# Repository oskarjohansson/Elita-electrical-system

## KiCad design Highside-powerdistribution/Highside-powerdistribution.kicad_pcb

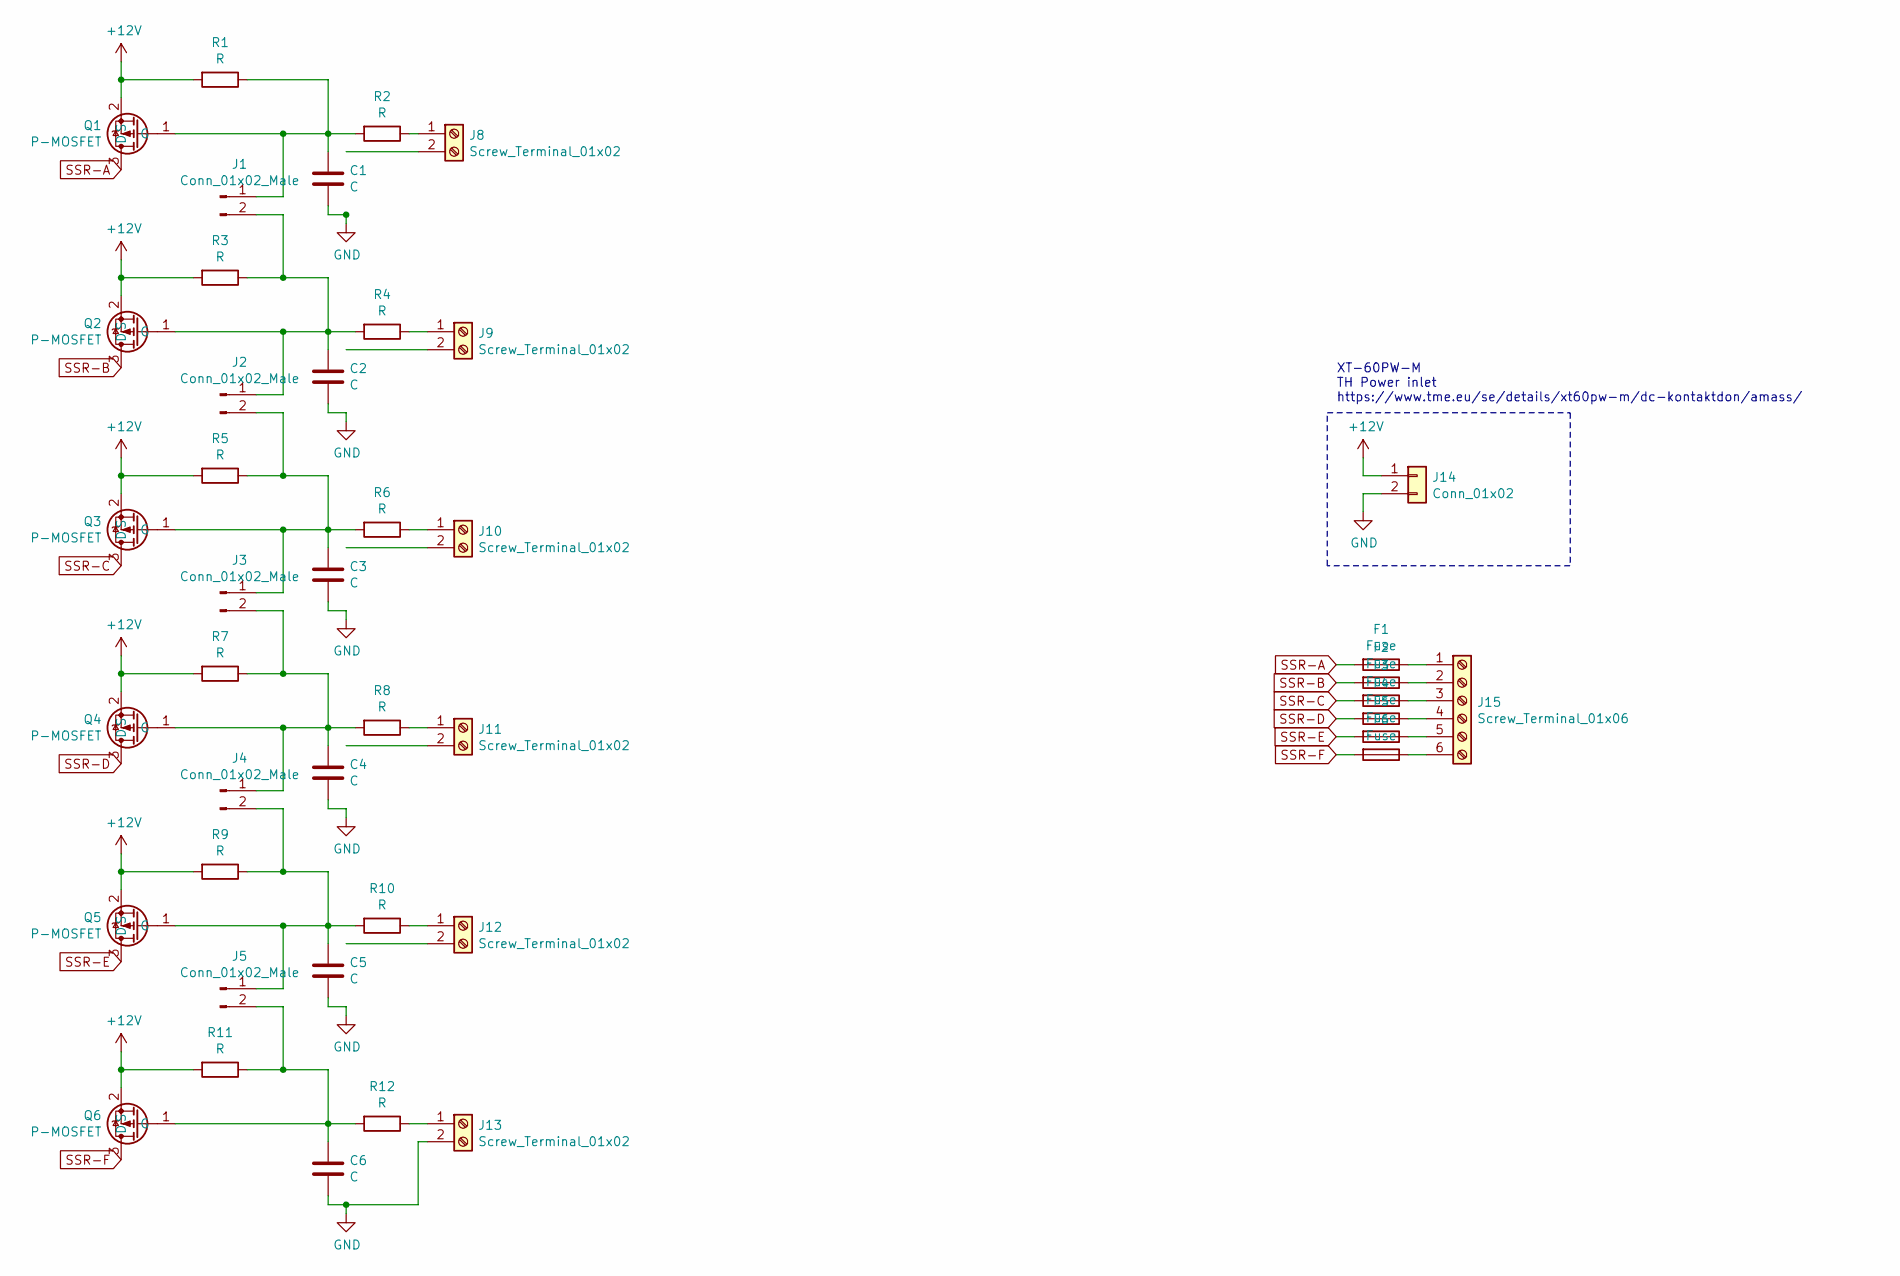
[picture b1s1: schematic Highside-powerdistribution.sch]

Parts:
C1, C2, C3, C4, C5, C6: C; C_0603_1608Metric_Pad1.05x0.95mm_HandSolder
F1, F2, F3, F4, F5, F6: Fuse; ATO_Fuseholder_3522-2
J1, J2, J3, J4, J5: Conn_01x02_Male; PinHeader_1x02_P2.54mm_Vertical
J8, J9, J10, J11, J12, J13: Screw_Terminal_01x02; PTSA1,5-2-3,5-Z
J14: Conn_01x02; Phoenix_TB_2-1935776
J15: Screw_Terminal_01x06; 20.101M-6
Q1, Q2, Q3, Q4, Q5, Q6: P-MOSFET; PG-TO263-3-2
R1, R2, R3, R4, R5, R6, R7, R8, R9, R10, R11, R12: R; R_0603_1608Metric_Pad1.05x0.95mm_HandSolder

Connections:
+12V: J14.1, Q1.2 (S), Q2.2 (S), Q3.2 (S), Q4.2 (S), Q5.2 (S), Q6.2 (S), R1.2, R3.2, R5.2, R7.2, R9.2, R11.2
GND: C1.2, C2.2, C3.2, C4.2, C5.2, C6.2, J8.2, J9.2, J10.2, J11.2, J12.2, J13.2, J14.2
unnamed: C1.1, J1.1, Q1.1 (G), R1.1, R2.2
unnamed: C2.1, J1.2, J2.1, Q2.1 (G), R3.1, R4.2
unnamed: C3.1, J2.2, J3.1, Q3.1 (G), R5.1, R6.2
unnamed: C4.1, J3.2, J4.1, Q4.1 (G), R7.1, R8.2
unnamed: C5.1, J4.2, J5.1, Q5.1 (G), R9.1, R10.2
unnamed: C6.1, J5.2, Q6.1 (G), R11.1, R12.2
unnamed: F1.1, J15.1
unnamed: F2.1, J15.2
unnamed: F3.1, J15.3
unnamed: F4.1, J15.4
unnamed: F5.1, J15.5
unnamed: F6.1, J15.6
unnamed: J8.1, R2.1
unnamed: J9.1, R4.1
unnamed: J10.1, R6.1
unnamed: J11.1, R8.1
unnamed: J12.1, R10.1
unnamed: J13.1, R12.1
SSR-A: F1.2, Q1.3 (D)
SSR-B: F2.2, Q2.3 (D)
SSR-C: F3.2, Q3.3 (D)
SSR-D: F4.2, Q4.3 (D)
SSR-E: F5.2, Q5.3 (D)
SSR-F: F6.2, Q6.3 (D)

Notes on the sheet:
XT-60PW-M TH Power inlet https://www.tme.eu/se/details/xt60pw-m/dc-kontaktdon/amass/

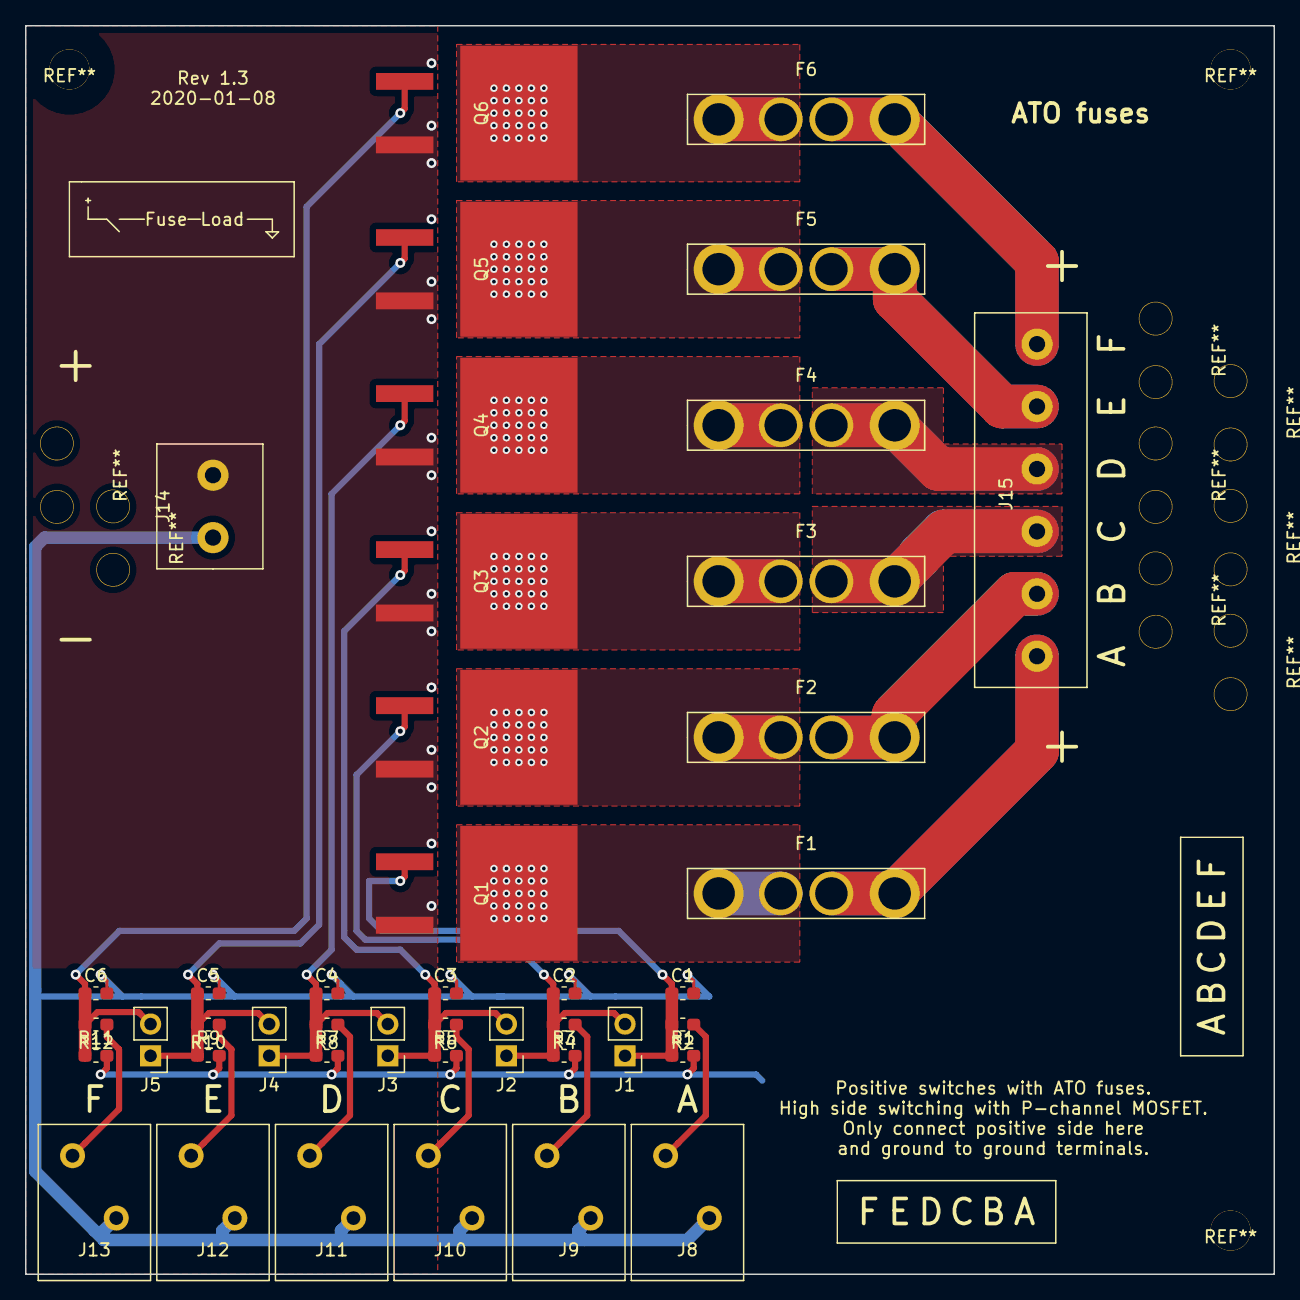
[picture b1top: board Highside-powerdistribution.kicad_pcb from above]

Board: 2 copper layers, 100.0 x 100.0 mm, 43 parts (0 on the bottom side), 26 nets.

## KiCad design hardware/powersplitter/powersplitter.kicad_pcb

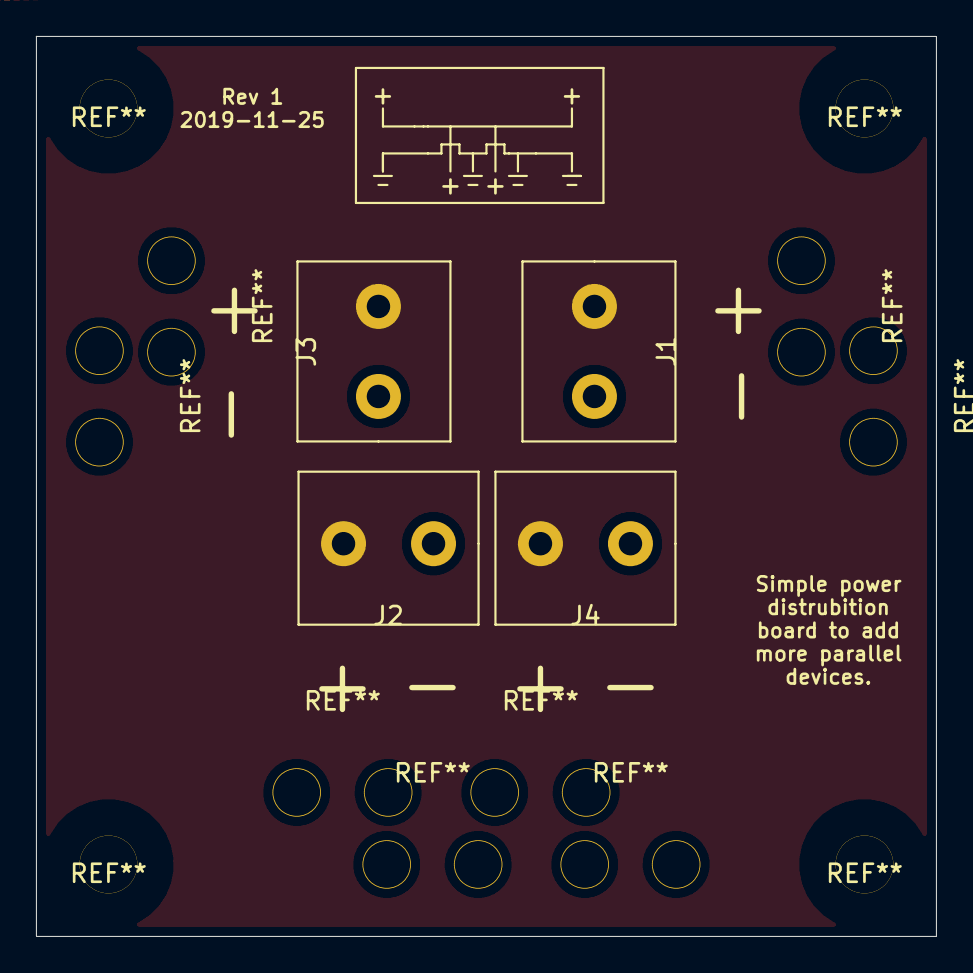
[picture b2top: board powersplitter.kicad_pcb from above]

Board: 2 copper layers, 50.0 x 50.0 mm, 4 parts (0 on the bottom side), 2 nets, no tracks yet.

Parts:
J1, J2, J3, J4: Screw_Terminal_01x02; Phoenix_TB_2-1935776

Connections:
+12V: J1.2, J2.1, J3.1, J4.1
GND: J1.1, J2.2, J3.2, J4.2
